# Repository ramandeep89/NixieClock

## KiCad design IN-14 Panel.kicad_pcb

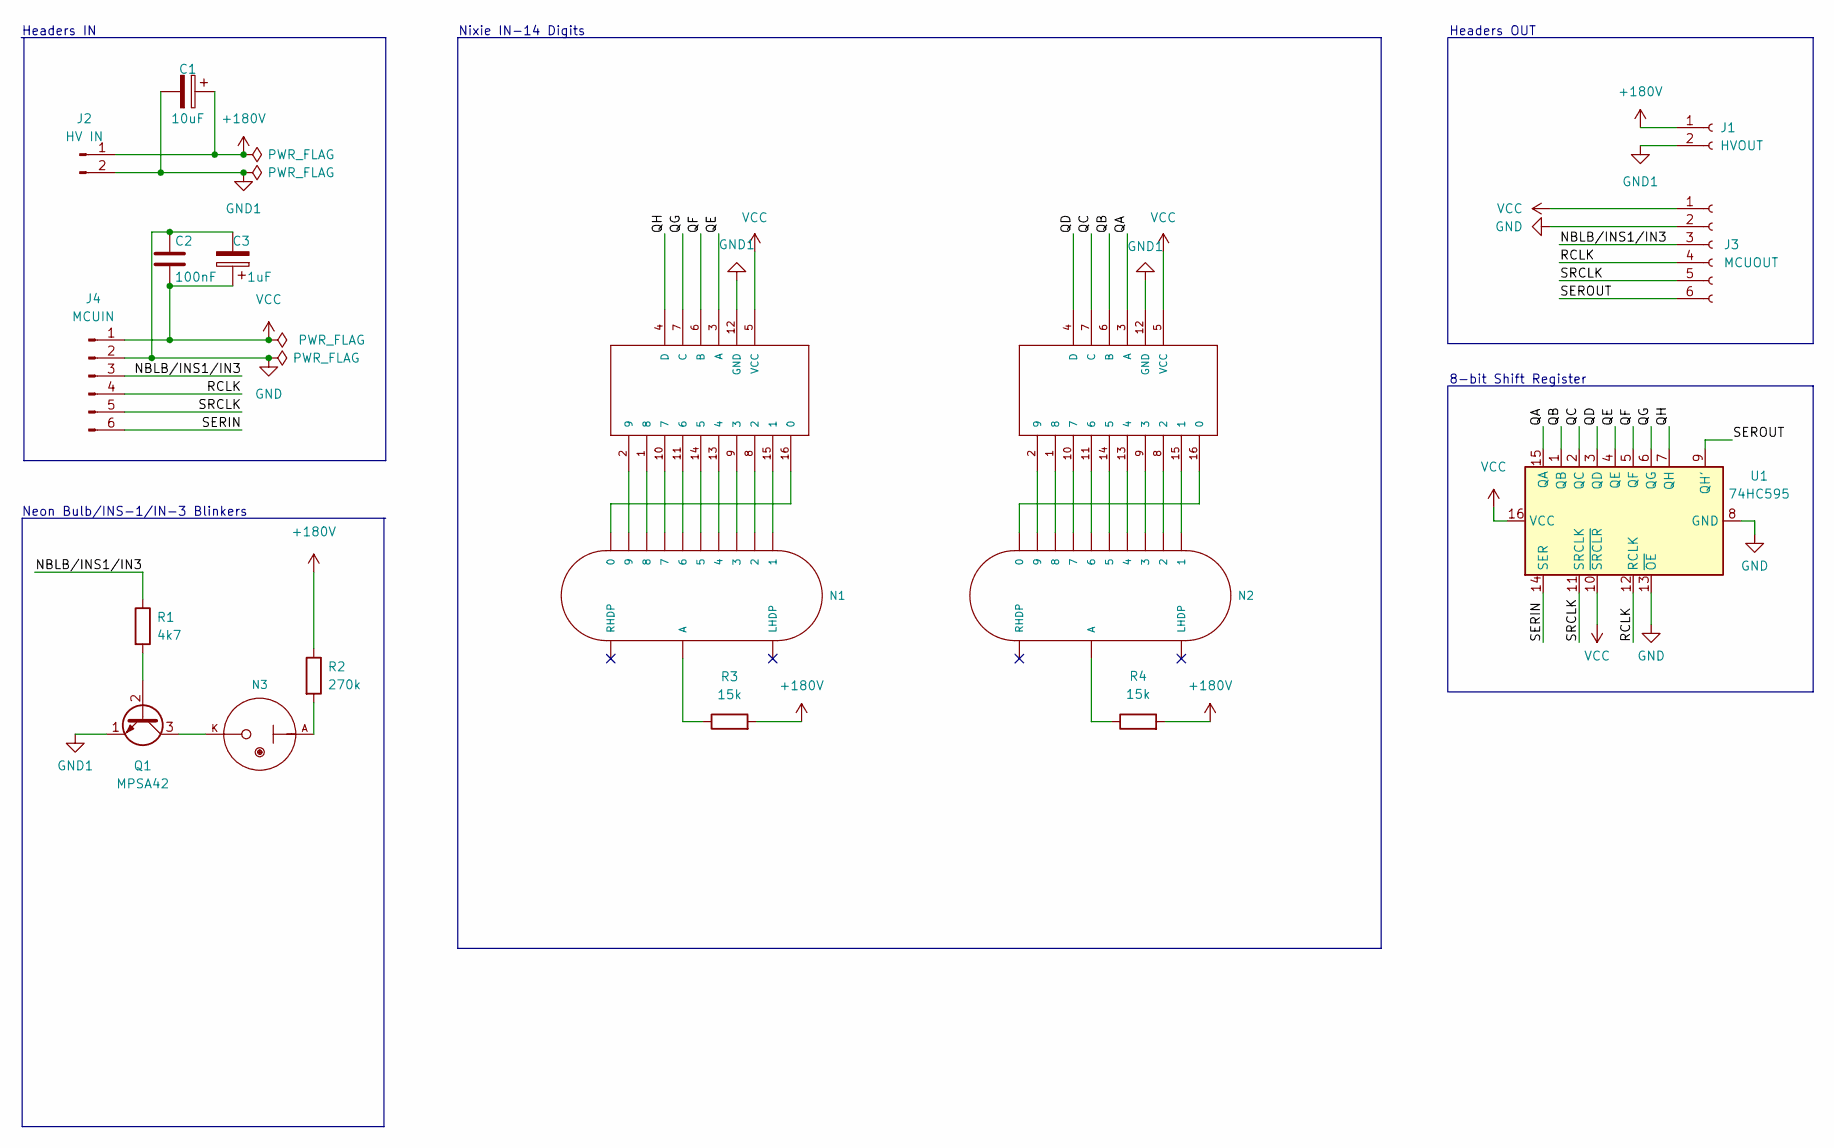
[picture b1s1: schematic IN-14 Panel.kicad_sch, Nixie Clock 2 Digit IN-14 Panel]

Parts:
C1: 10uF; CP_Radial_D10.0mm_P5.00mm
C2: 100nF; C_Disc_D3.0mm_W2.0mm_P2.50mm
C3: 1uF; CP_Radial_D5.0mm_P2.00mm
J1: HVOUT; PinHeader_1x02_P2.54mm_Vertical
J2: HV IN; PinHeader_1x02_P2.54mm_Vertical
J3: MCUOUT; PinHeader_1x06_P2.54mm_Vertical
J4: MCUIN; PinHeader_1x06_P2.54mm_Vertical
M1, M2: 74141DIP16; DIP-16_W7.62mm
N1, N2: IN-14; nixies-us-IN-14
N3: IN-3; nixies-us-IN-3
Q1: MPSA42; TO-92_Inline
R1: 4k7; R_Axial_DIN0207_L6.3mm_D2.5mm_P7.62mm_Horizontal
R2: 270k; R_Axial_DIN0207_L6.3mm_D2.5mm_P7.62mm_Horizontal
R3, R4: 15k; R_Axial_DIN0207_L6.3mm_D2.5mm_P7.62mm_Horizontal
U1: 74HC595; DIP-16_W7.62mm

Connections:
+180V: C1.1, J1.1, J2.1, R2.1, R3.2, R4.2
/NBLB/INS1/IN3: J3.3, J4.3, R1.1
/QA: M2.3 (A), U1.15 (QA)
/QB: M2.6 (B), U1.1 (QB)
/QC: M2.7 (C), U1.2 (QC)
/QD: M2.4 (D), U1.3 (QD)
/QE: M1.3 (A), U1.4 (QE)
/QF: M1.6 (B), U1.5 (QF)
/QG: M1.7 (C), U1.6 (QG)
/QH: M1.4 (D), U1.7 (QH)
/RCLK: J3.4, J4.4, U1.12 (RCLK)
/SERIN: J4.6, U1.14 (SER)
/SEROUT: J3.6, U1.9 (QH')
/SRCLK: J3.5, J4.5, U1.11 (SRCLK)
GND: C2.1, C3.2, J3.2, J4.2, U1.8 (GND), U1.13 (~OE)
GND1: C1.2, J1.2, J2.2, M1.12 (GND), M2.12 (GND), Q1.1 (E)
unnamed: M1.1 (8), N1.8
unnamed: M1.2 (9), N1.9
unnamed: M1.8 (2), N1.2
unnamed: M1.9 (3), N1.3
unnamed: M1.10 (7), N1.7
unnamed: M1.11 (6), N1.6
unnamed: M1.13 (4), N1.4
unnamed: M1.14 (5), N1.5
unnamed: M1.15 (1), N1.1
unnamed: M1.16 (0), N1.0
unnamed: M2.1 (8), N2.8
unnamed: M2.2 (9), N2.9
unnamed: M2.8 (2), N2.2
unnamed: M2.9 (3), N2.3
unnamed: M2.10 (7), N2.7
unnamed: M2.11 (6), N2.6
unnamed: M2.13 (4), N2.4
unnamed: M2.14 (5), N2.5
unnamed: M2.15 (1), N2.1
unnamed: M2.16 (0), N2.0
unnamed: N1.A, R3.1
unnamed: N2.A, R4.1
unnamed: N3.A, R2.2
unnamed: N3.K, Q1.3 (C)
unnamed: Q1.2 (B), R1.2
VCC: C2.2, C3.1, J3.1, J4.1, M1.5 (VCC), M2.5 (VCC), U1.10 (~SRCLR), U1.16 (VCC)

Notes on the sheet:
Headers OUT
Headers IN
Nixie IN-14 Digits
Neon Bulb/INS-1/IN-3 Blinkers
8-bit Shift Register

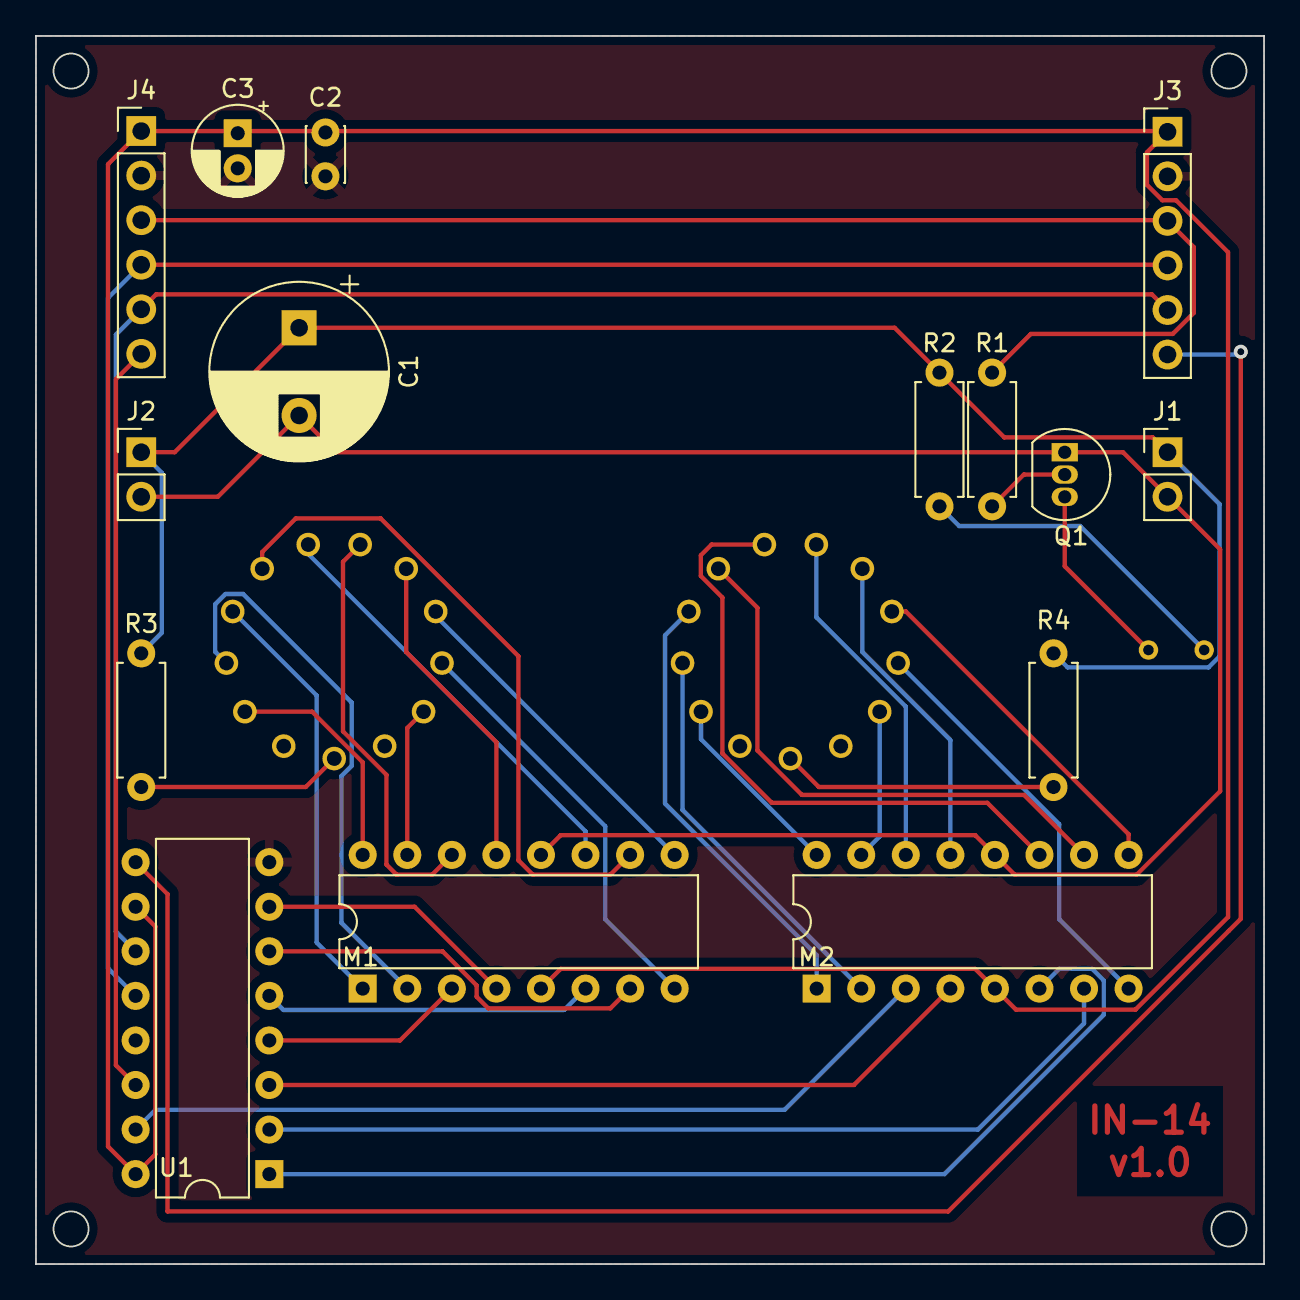
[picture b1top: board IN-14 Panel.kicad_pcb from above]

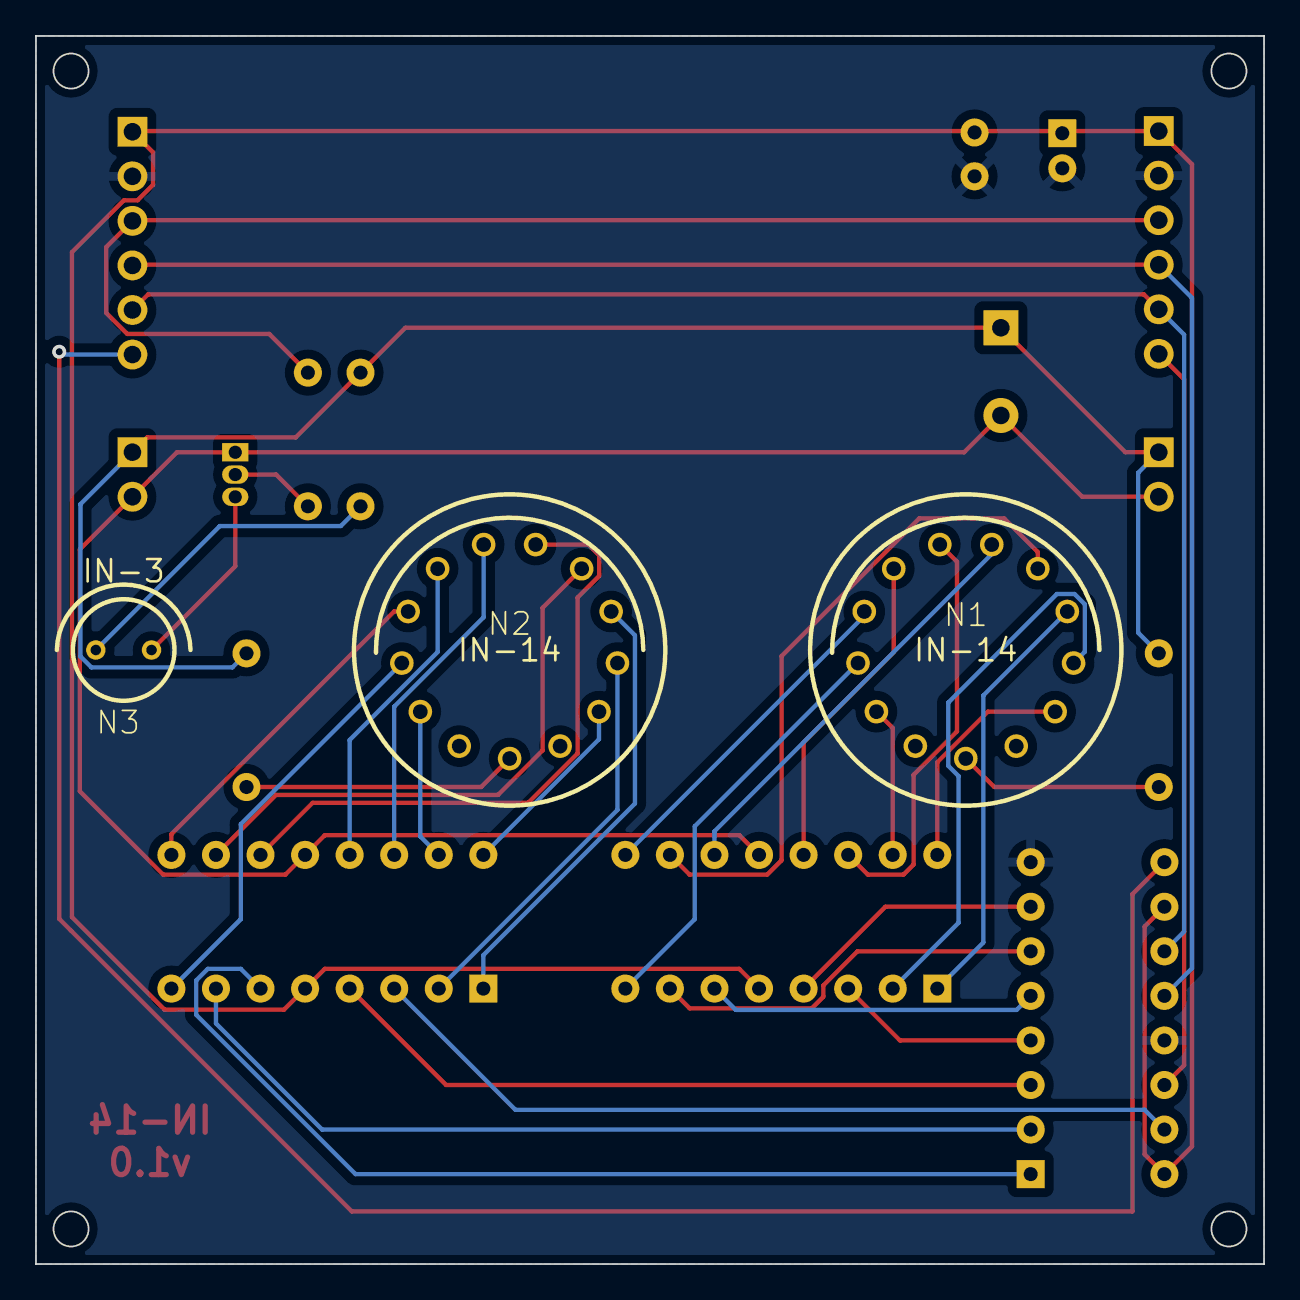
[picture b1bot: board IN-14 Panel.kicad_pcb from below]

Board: 2 copper layers, 70.0 x 70.0 mm, 18 parts (3 on the bottom side), 42 nets.
